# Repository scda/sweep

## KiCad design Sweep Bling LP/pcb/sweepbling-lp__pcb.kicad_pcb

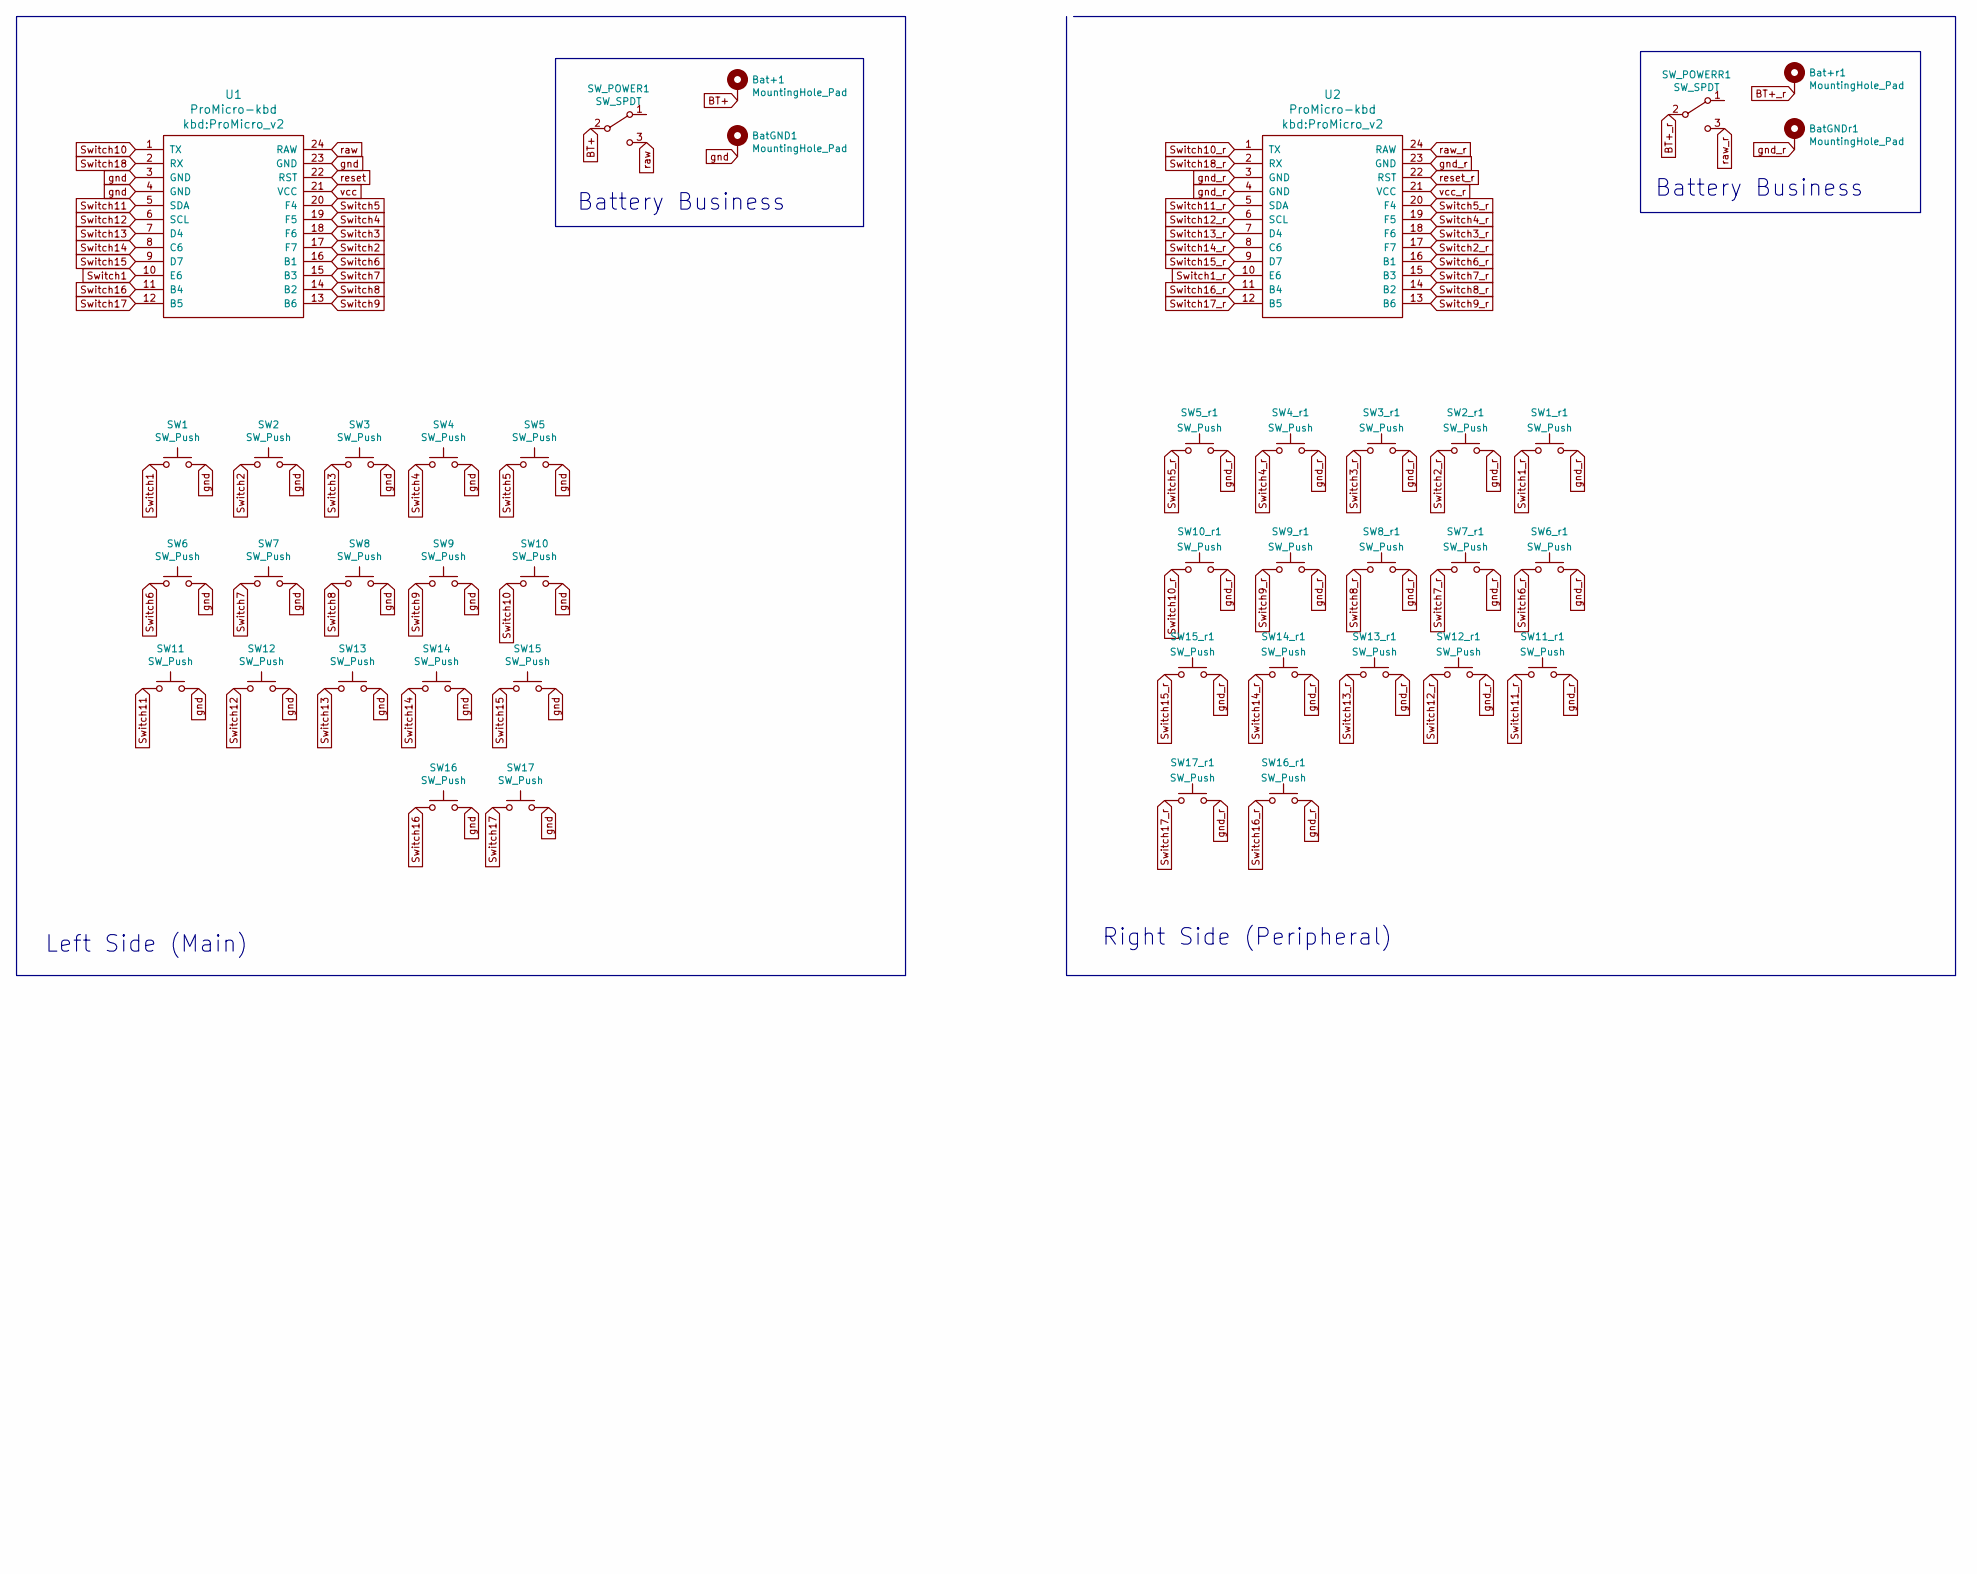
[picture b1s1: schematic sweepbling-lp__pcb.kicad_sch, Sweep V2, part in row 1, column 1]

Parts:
Bat+1: MountingHole_Pad; 1pin_conn
Bat+r1: MountingHole_Pad; 1pin_conn
BatGND1: MountingHole_Pad; 1pin_conn
BatGNDr1: MountingHole_Pad; 1pin_conn
SW1, SW1_r1, SW2, SW2_r1, SW3, SW3_r1, SW4, SW4_r1, SW5, SW5_r1, SW6, SW6_r1, SW7, SW7_r1, SW8, SW8_r1, SW9, SW9_r1, SW10, SW10_r1, SW11, SW11_r1, SW12, SW12_r1, SW13, SW13_r1, SW14, SW14_r1, SW15, SW15_r1, SW16, SW16_r1, SW17, SW17_r1: SW_Push; SW_PG1350_rev_DPB
SW_POWER1: SW_SPDT; SPDT_C128955
SW_POWERR1: SW_SPDT; SPDT_C128955
U1, U2: ProMicro-kbd; ProMicro_v2

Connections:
BT+: Bat+1.1, SW_POWER1.2 (B)
BT+_r: Bat+r1.1, SW_POWERR1.2 (B)
Switch1: SW1.1, U1.10 (E6)
Switch1_r: SW1_r1.1, U2.10 (E6)
Switch2: SW2.1, U1.17 (F7)
Switch2_r: SW2_r1.1, U2.17 (F7)
Switch3: SW3.1, U1.18 (F6)
Switch3_r: SW3_r1.1, U2.18 (F6)
Switch4: SW4.1, U1.19 (F5)
Switch4_r: SW4_r1.1, U2.19 (F5)
Switch5: SW5.1, U1.20 (F4)
Switch5_r: SW5_r1.1, U2.20 (F4)
Switch6: SW6.1, U1.16 (B1)
Switch6_r: SW6_r1.1, U2.16 (B1)
Switch7: SW7.1, U1.15 (B3)
Switch7_r: SW7_r1.1, U2.15 (B3)
Switch8: SW8.1, U1.14 (B2)
Switch8_r: SW8_r1.1, U2.14 (B2)
Switch9: SW9.1, U1.13 (B6)
Switch9_r: SW9_r1.1, U2.13 (B6)
Switch10: SW10.1, U1.1 (TX)
Switch10_r: SW10_r1.1, U2.1 (TX)
Switch11: SW11.1, U1.5 (SDA)
Switch11_r: SW11_r1.1, U2.5 (SDA)
Switch12: SW12.1, U1.6 (SCL)
Switch12_r: SW12_r1.1, U2.6 (SCL)
Switch13: SW13.1, U1.7 (D4)
Switch13_r: SW13_r1.1, U2.7 (D4)
Switch14: SW14.1, U1.8 (C6)
Switch14_r: SW14_r1.1, U2.8 (C6)
Switch15: SW15.1, U1.9 (D7)
Switch15_r: SW15_r1.1, U2.9 (D7)
Switch16: SW16.1, U1.11 (B4)
Switch16_r: SW16_r1.1, U2.11 (B4)
Switch17: SW17.1, U1.12 (B5)
Switch17_r: SW17_r1.1, U2.12 (B5)
Switch18: U1.2 (RX)
Switch18_r: U2.2 (RX)
gnd: BatGND1.1, SW1.2, SW2.2, SW3.2, SW4.2, SW5.2, SW6.2, SW7.2, SW8.2, SW9.2, SW10.2, SW11.2, SW12.2, SW13.2, SW14.2, SW15.2, SW16.2, SW17.2, U1.3 (GND), U1.4 (GND), U1.23 (GND)
gnd_r: BatGNDr1.1, SW1_r1.2, SW2_r1.2, SW3_r1.2, SW4_r1.2, SW5_r1.2, SW6_r1.2, SW7_r1.2, SW8_r1.2, SW9_r1.2, SW10_r1.2, SW11_r1.2, SW12_r1.2, SW13_r1.2, SW14_r1.2, SW15_r1.2, SW16_r1.2, SW17_r1.2, U2.3 (GND), U2.4 (GND), U2.23 (GND)
raw: SW_POWER1.3 (C), U1.24 (RAW)
raw_r: SW_POWERR1.3 (C), U2.24 (RAW)
reset: U1.22 (RST)
reset_r: U2.22 (RST)
vcc: U1.21 (VCC)
vcc_r: U2.21 (VCC)

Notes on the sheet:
Battery Business
Left Side (Main)
Right Side (Peripheral)

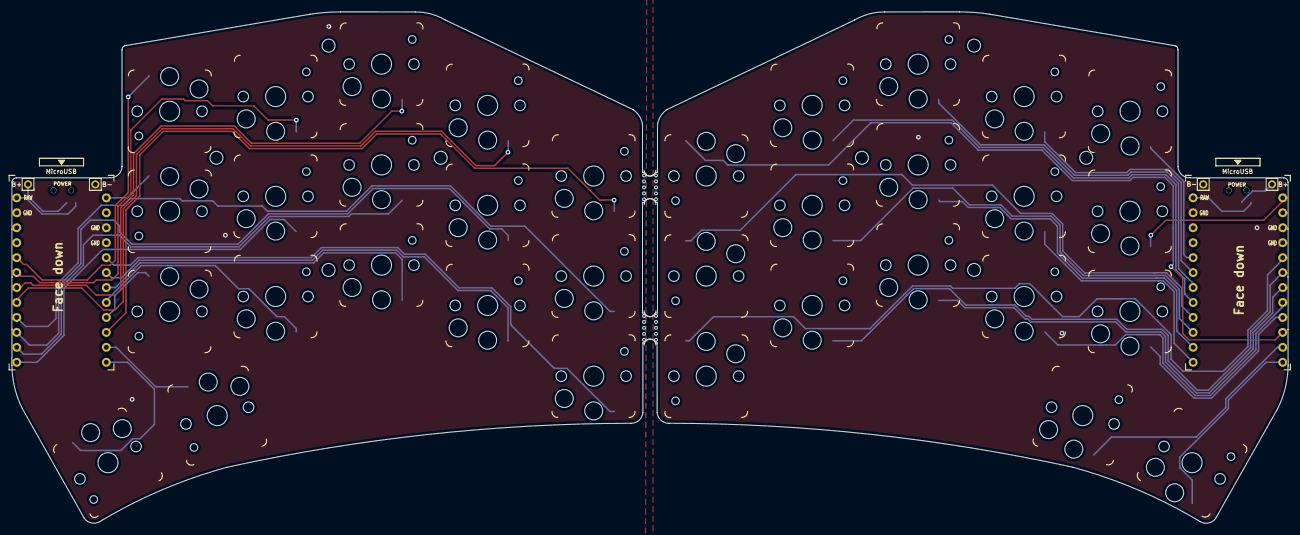
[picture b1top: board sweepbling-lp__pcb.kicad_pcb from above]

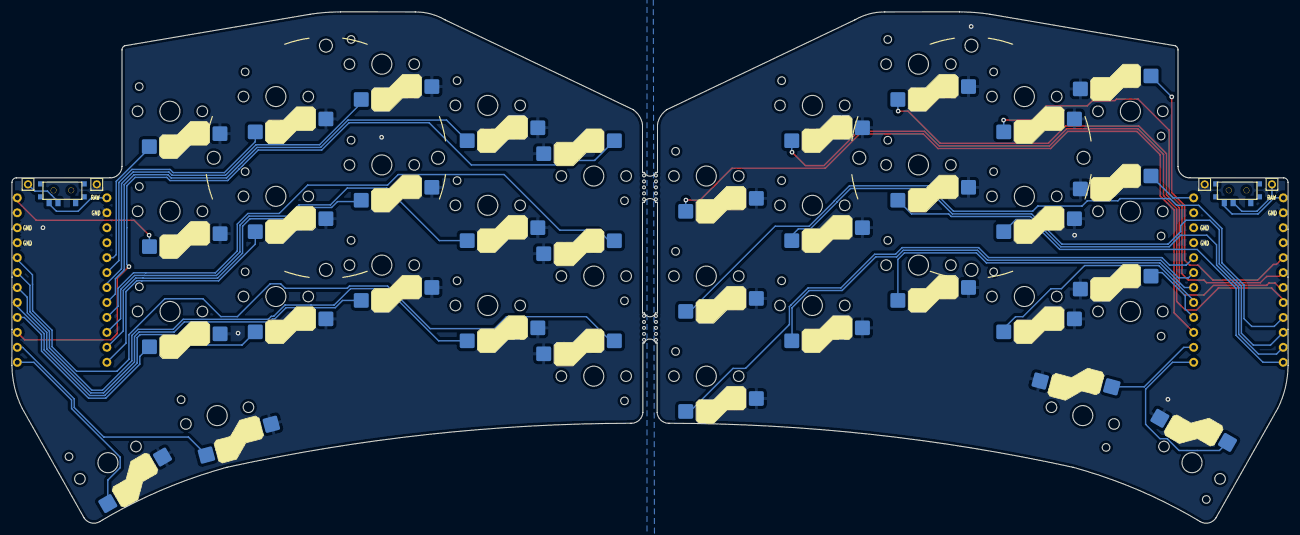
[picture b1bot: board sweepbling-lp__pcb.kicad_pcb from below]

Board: 2 copper layers, 216.8 x 86.9 mm, 46 parts (2 on the bottom side), 40 nets.

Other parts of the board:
REF_PUCK_R: Tenting Puck; Tenting_Puck2_no_pads_no_text
e: Tenting Puck; Tenting_Puck2_no_pads_no_text
mouse-bite-2mm-slot1, mouse-bite-2mm-slot2: VAL**; mouse-bite-5mm-slot-with-space-for-track

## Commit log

2022-08-24 remove crab logo
2022-08-24 reduce tenting pucks
2022-08-24 remove version silk
2022-08-24 remove trrs ports and connections
2022-08-24 replace key markings
2022-08-24 move reset buttons
2022-09-14 drop reset pads
2022-09-15 change outline right side
2022-09-15 redo edge cuts and mirror
2022-09-30 create gerber output for v0
2022-10-20 re-set copper zones
2022-10-20 new gerber output
2022-11-02 add drill files to gerbers
